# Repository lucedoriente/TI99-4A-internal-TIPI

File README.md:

This projct born to integrate the ElectricLab & Jedimatt42 TIPI board in the new TI99/4A version by Dan Werner.
I like so much this project and adding TIPI features without external box or usin PEB seems to me a great idea.
Maybe it's not but I like it.

License
The original project was licensed under the Creative Commons - Attribution - ShareAlike 3.0 License

Attribution
This board was derrived from works by, uses design elements from, or contains sofware writen by the following:

Matthew Splett - jedimatt42 (https://github.com/jedimatt42/tipi.git)

Inspired by the Dan Werner beautiful TI99-22 project:

Dan Werner (https://github.com/danwerner21/TI99_22.git)

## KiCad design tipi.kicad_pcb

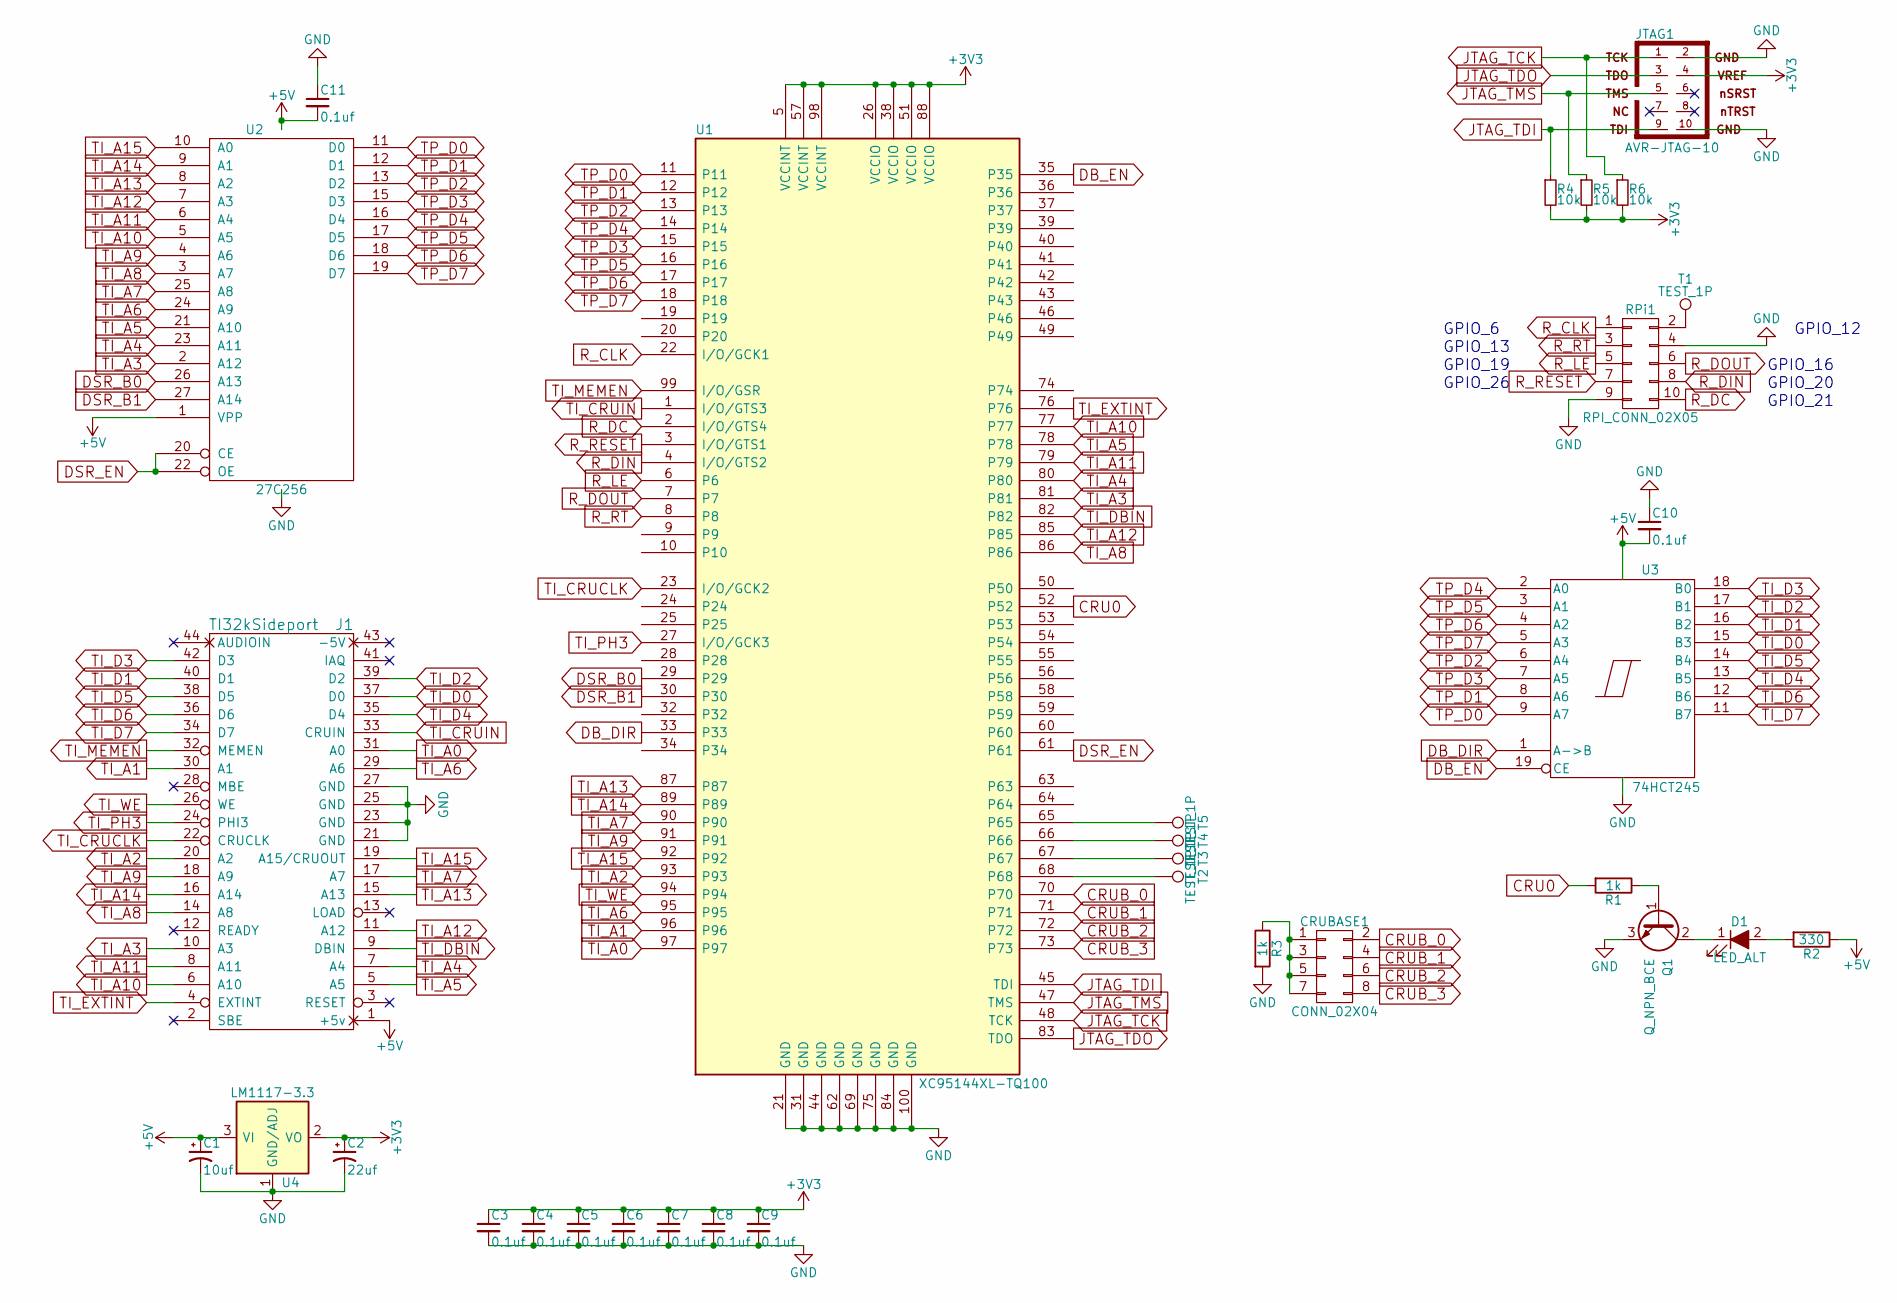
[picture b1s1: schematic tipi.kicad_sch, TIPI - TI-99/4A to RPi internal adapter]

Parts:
C1: 10uf; C_0805_2012Metric_Pad1.18x1.45mm_HandSolder
C2: 22uf; C_0805_2012Metric_Pad1.18x1.45mm_HandSolder
C3, C4, C5, C6, C7, C8, C9, C10, C11: 0.1uf; C_0805_2012Metric_Pad1.18x1.45mm_HandSolder
CRUBASE1: CONN_02X04; PinHeader_2x04_P2.54mm_Vertical
D1: LED_ALT; LED_D3.0mm
J1: TI32kSideport; PinSocket_2x22_P2.54mm_Vertical
JTAG1: AVR-JTAG-10; IDC-Header_2x05_P2.54mm_Vertical
Q1: Q_NPN_BCE; SOT-23
R1, R3: 1k; R_0805_2012Metric_Pad1.20x1.40mm_HandSolder
R2: 330; R_0805_2012Metric_Pad1.20x1.40mm_HandSolder
R4, R5, R6: 10k; R_0805_2012Metric_Pad1.20x1.40mm_HandSolder
RPi1: RPI_CONN_02X05; IDC-Header_2x05_P2.54mm_Vertical
T1, T2, T3, T4, T5: TEST_1P; SolderWirePad_1x01_SMD_1x2mm
U1: XC95144XL-TQ100; TQFP-100_14x14mm_P0.5mm
U2: 27C256; DIP-28_W15.24mm_Socket
U3: 74HCT245; SSOP-20_3.9x8.7mm_P0.635mm
U4: LM1117-3.3; SOT-223

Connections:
+3V3: C2.1, C3.1, C4.1, C5.1, C6.1, C7.1, C8.1, C9.1, JTAG1.4, R4.2, R5.2, R6.2, U1.5 (VCCINT), U1.26 (VCCIO), U1.38 (VCCIO), U1.51 (VCCIO), U1.57 (VCCINT), U1.88 (VCCIO), U1.98 (VCCINT), U4.2 (VO), U4.4 (VO)
+5V: C1.1, C10.2, C11.2, J1.1 (+5v), R2.1, U2.1 (VPP), U2.28 (VCC), U3.20 (VCC), U4.3 (VI)
CRU0: R1.2, U1.52
CRUB_0: CRUBASE1.2, U1.70
CRUB_1: CRUBASE1.4, U1.71
CRUB_2: CRUBASE1.6, U1.72
CRUB_3: CRUBASE1.8, U1.73
DB_DIR: U1.33, U3.1 (A->B)
DB_EN: U1.35, U3.19 (CE)
DSR_B0: U1.29, U2.26 (A13)
DSR_B1: U1.30, U2.27 (A14)
DSR_EN: U1.61, U2.20 (CE), U2.22 (OE)
GND: C1.2, C2.2, C3.2, C4.2, C5.2, C6.2, C7.2, C8.2, C9.2, C10.1, C11.1, J1.21 (GND), J1.23 (GND), J1.25 (GND), J1.27 (GND), JTAG1.2, JTAG1.10, Q1.3 (E), R3.2, RPi1.4, RPi1.9, U1.21 (GND), U1.31 (GND), U1.44 (GND), U1.62 (GND), U1.69 (GND), U1.75 (GND), U1.84 (GND), U1.100 (GND), U2.14 (GND), U3.10 (GND), U4.1 (GND/ADJ)
JTAG_TCK: JTAG1.1, R6.1, U1.48 (TCK)
JTAG_TDI: JTAG1.9, R4.1, U1.45 (TDI)
JTAG_TDO: JTAG1.3, U1.83 (TDO)
JTAG_TMS: JTAG1.5, R5.1, U1.47 (TMS)
unnamed: CRUBASE1.1, CRUBASE1.3, CRUBASE1.5, CRUBASE1.7, R3.1
unnamed: D1.2 (A), R2.2
unnamed: D1.1 (K), Q1.2 (C)
unnamed: Q1.1 (B), R1.1
unnamed: RPi1.2, T1.1
unnamed: T5.1, U1.65
unnamed: T4.1, U1.66
unnamed: T3.1, U1.67
unnamed: T2.1, U1.68
R_CLK: RPi1.1, U1.22 (I/O/GCK1)
R_DC: RPi1.10, U1.2 (I/O/GTS4)
R_DIN: RPi1.8, U1.4 (I/O/GTS2)
R_DOUT: RPi1.6, U1.7
R_LE: RPi1.5, U1.6
R_RESET: RPi1.7, U1.3 (I/O/GTS1)
R_RT: RPi1.3, U1.8
TI_A0: J1.31 (A0), U1.97
TI_A1: J1.30 (A1), U1.96
TI_A2: J1.20 (A2), U1.93
TI_A3: J1.10 (A3), U1.81, U2.2 (A12)
TI_A4: J1.7 (A4), U1.80, U2.23 (A11)
TI_A5: J1.5 (A5), U1.78, U2.21 (A10)
TI_A6: J1.29 (A6), U1.95, U2.24 (A9)
TI_A7: J1.17 (A7), U1.90, U2.25 (A8)
TI_A8: J1.14 (A8), U1.86, U2.3 (A7)
TI_A9: J1.18 (A9), U1.91, U2.4 (A6)
TI_A10: J1.6 (A10), U1.77, U2.5 (A5)
TI_A11: J1.8 (A11), U1.79, U2.6 (A4)
TI_A12: J1.11 (A12), U1.85, U2.7 (A3)
TI_A13: J1.15 (A13), U1.87, U2.8 (A2)
TI_A14: J1.16 (A14), U1.89, U2.9 (A1)
TI_A15: J1.19 (A15/CRUOUT), U1.92, U2.10 (A0)
TI_CRUCLK: J1.22 (CRUCLK), U1.23 (I/O/GCK2)
TI_CRUIN: J1.33 (CRUIN), U1.1 (I/O/GTS3)
TI_D0: J1.37 (D0), U3.15 (B3)
TI_D1: J1.40 (D1), U3.16 (B2)
TI_D2: J1.39 (D2), U3.17 (B1)
TI_D3: J1.42 (D3), U3.18 (B0)
TI_D4: J1.35 (D4), U3.13 (B5)
TI_D5: J1.38 (D5), U3.14 (B4)
TI_D6: J1.36 (D6), U3.12 (B6)
TI_D7: J1.34 (D7), U3.11 (B7)
TI_DBIN: J1.9 (DBIN), U1.82
TI_EXTINT: J1.4 (EXTINT), U1.76
TI_MEMEN: J1.32 (MEMEN), U1.99 (I/O/GSR)
TI_PH3: J1.24 (PHI3), U1.27 (I/O/GCK3)
TI_WE: J1.26 (WE), U1.94
TP_D0: U1.11, U2.11 (D0), U3.9 (A7)
TP_D1: U1.12, U2.12 (D1), U3.8 (A6)
TP_D2: U1.13, U2.13 (D2), U3.6 (A4)
TP_D3: U1.15, U2.15 (D3), U3.7 (A5)
TP_D4: U1.14, U2.16 (D4), U3.2 (A0)
TP_D5: U1.16, U2.17 (D5), U3.3 (A1)
TP_D6: U1.17, U2.18 (D6), U3.4 (A2)
TP_D7: U1.18, U2.19 (D7), U3.5 (A3)

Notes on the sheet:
GPIO_20
GPIO_13
GPIO_19
GPIO_26
GPIO_12
GPIO_6
GPIO_16
GPIO_21

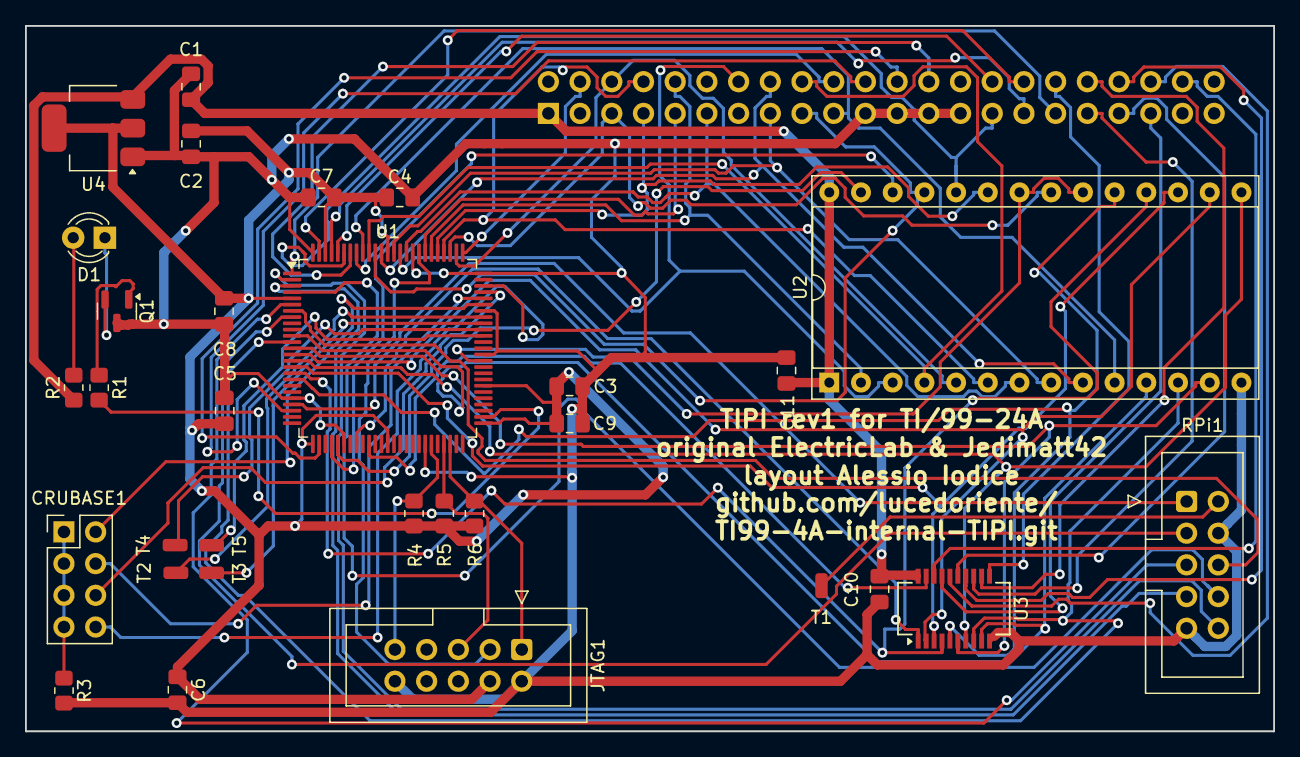
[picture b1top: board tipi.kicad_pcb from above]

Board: 2 copper layers, 100.0 x 56.5 mm, 32 parts (1 on the bottom side), 72 nets.

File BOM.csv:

'Reference';'Value';'Datasheet';'Footprint';'Qty';'DNP'
'C1';'10uf';'';'Capacitor_SMD:C_0805_2012Metric_Pad1.18x1.45mm_HandSolder';'1';''
'C2';'22uf';'';'Capacitor_SMD:C_0805_2012Metric_Pad1.18x1.45mm_HandSolder';'1';''
'C3,C4,C5,C6,C7,C8,C9,C10,C11';'0.1uf';'';'Capacitor_SMD:C_0805_2012Metric_Pad1.18x1.45mm_HandSolder';'9';''
'CRUBASE1';'CONN_02X04';'';'Connector_PinHeader_2.54mm:PinHeader_2x04_P2.54mm_Vertical';'1';''
'D1';'LED_ALT';'';'LED_THT:LED_D3.0mm';'1';''
'J1';'TI32kSideport';'';'Connector_PinSocket_2.54mm:PinSocket_2x22_P2.54mm_Vertical';'1';''
'JTAG1';'AVR-JTAG-10';'';'Connector_IDC:IDC-Header_2x05_P2.54mm_Vertical';'1';''
'Q1';'Q_NPN_BCE';'';'Package_TO_SOT_SMD:SOT-23';'1';''
'R1,R3';'1k';'';'Resistor_SMD:R_0805_2012Metric_Pad1.20x1.40mm_HandSolder';'2';''
'R2';'330';'';'Resistor_SMD:R_0805_2012Metric_Pad1.20x1.40mm_HandSolder';'1';''
'R4,R5,R6';'10k';'';'Resistor_SMD:R_0805_2012Metric_Pad1.20x1.40mm_HandSolder';'3';''
'RPi1';'RPI_CONN_02X05';'';'Connector_IDC:IDC-Header_2x05_P2.54mm_Vertical';'1';''
'T1,T2,T3,T4,T5';'TEST_1P';'';'Connector_Wire:SolderWirePad_1x01_SMD_1x2mm';'5';''
'U1';'XC95144XL-TQ100';'';'Package_QFP:TQFP-100_14x14mm_P0.5mm';'1';''
'U2';'27C256';'';'Package_DIP:DIP-28_W15.24mm_Socket';'1';''
'U3';'74HCT245';'';'Package_SO:SSOP-20_3.9x8.7mm_P0.635mm';'1';''
'U4';'LM1117-3.3';'';'Package_TO_SOT_SMD:SOT-223';'1';''

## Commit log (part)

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2024-04-11 Add files via upload
    First commit
2024-04-11 Add files via upload
    BOM added
2024-04-11 Create LICENSE
